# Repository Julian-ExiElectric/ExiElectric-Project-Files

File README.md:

# ExiElectric-Project-Files
Completed projects to be stored

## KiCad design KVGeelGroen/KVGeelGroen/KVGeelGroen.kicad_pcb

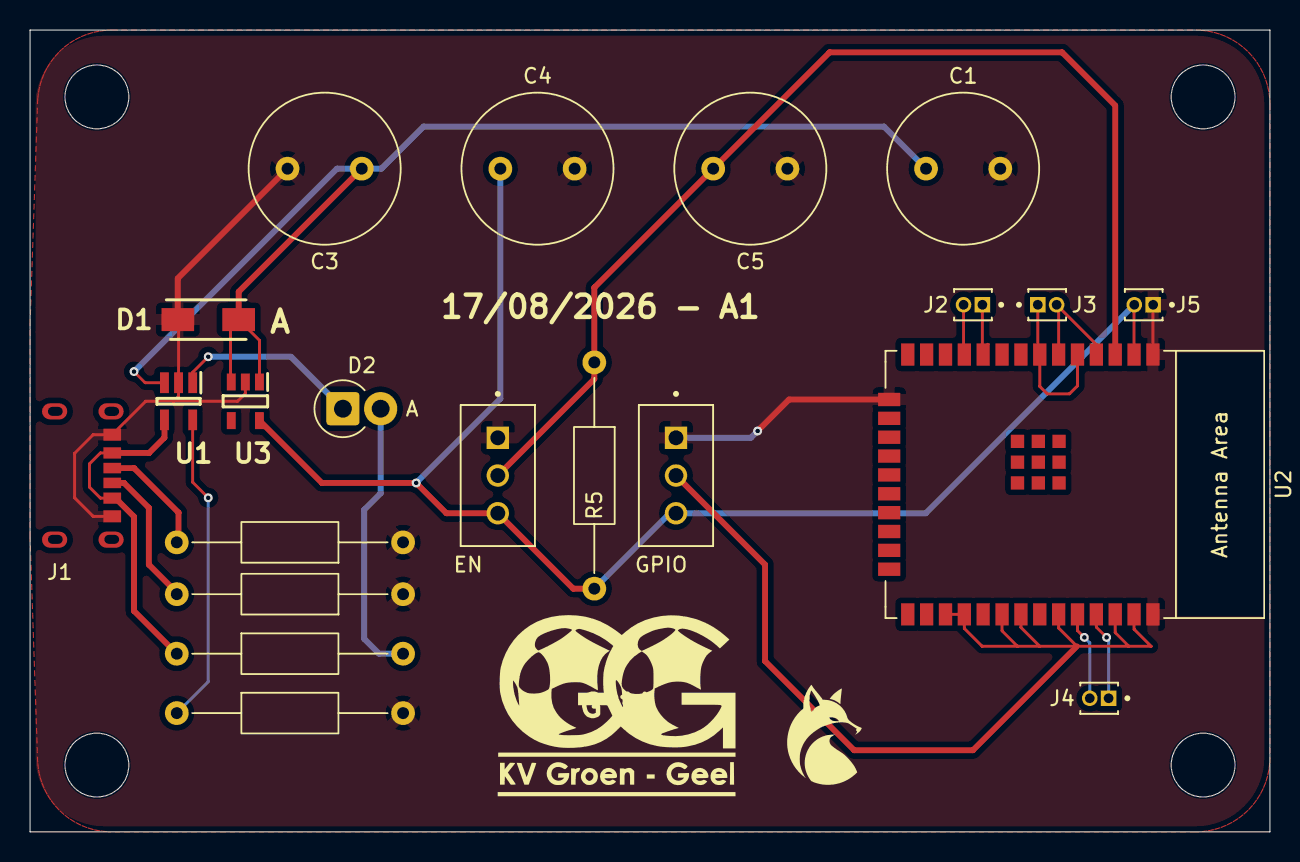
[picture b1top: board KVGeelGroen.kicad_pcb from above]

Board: 2 copper layers, 83.5 x 54.0 mm, 22 parts (0 on the bottom side), 17 nets.

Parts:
1: LOGO; CuteFox
C1: 5.6uF; C_Radial_D10.0mm_H12.5mm_P5.00mm
C3, C4, C5: 1uF; C_Radial_D10.0mm_H12.5mm_P5.00mm
D1: SMAJ5.0A-E3_61
D2: TEMP; D_DO-15_P2.54mm_Vertical_AnodeUp
EN: ATE1D-2M3-10-Z; SW_ATE1D-2M3-10-Z
GPIO: ATE1D-2M3-10-Z; SW_ATE1D-2M3-10-Z
J1: USB-C-MOLEX; 2171750001_MOL
J2, J3, J4, J5: M50-3530242; HARWIN_M50-3530242
R1: 2K; R_Axial_DIN0207_L6.3mm_D2.5mm_P15.24mm_Horizontal
R2: 75; R_Axial_DIN0207_L6.3mm_D2.5mm_P15.24mm_Horizontal
R3, R4: 5.1K; R_Axial_DIN0207_L6.3mm_D2.5mm_P15.24mm_Horizontal
R5: 10K; R_Axial_DIN0207_L6.3mm_D2.5mm_P15.24mm_Horizontal
U1: MCP73831T-2ACI_OT; MCP73831
U2: ESP32-WROOM-E; ESP32-WROOM-32E
U3: AP2112K-3V3; AP2112K

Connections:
+3V3: C4.1, EN.3, GPIO.3, J5.2, R5.2, U2.2 (3V3), U3.5 (VOUT)
+BATT: C1.1, C3.1, D1.2 (A), U1.3 (VBAT), U3.1 (VIN), U3.3 (EN)
GND: C1.2, C3.2, C4.2, C5.1, D1.1 (K), EN.1, GPIO.1, J1.A12 (GND_2), J1.B12 (GND), J5.1, R1.2, R3.1, R4.1, U1.2 (VSS), U2.1 (GND), U2.15 (GND), U2.38 (GND), U3.2 (GND)
unnamed: D2.2 (A), R2.2
unnamed: D2.1 (K), U1.1 (STAT)
unnamed: J1.A5 (CC1), R3.2
unnamed: J1.B5 (CC2), R4.2
unnamed: R1.1, U1.5 (PROG)
unnamed: J2.1, U2.10 (DAC_1/ADC2_CH8/GPIO25)
unnamed: J2.2, U2.11 (DAC_2/ADC2_CH9/GPIO26)
unnamed: C5.2, EN.2, R5.1, U2.3 (EN/CHIP_PU)
unnamed: GPIO.2, U2.27 (GPIO16), U2.28 (GPIO17), U2.30 (GPIO18), U2.31 (GPIO19), U2.33 (GPIO21), U2.36 (GPIO22), U2.37 (GPIO23)
unnamed: J3.2, U2.4 (SENSOR_VP/GPIO36/ADC1_CH0), U2.6 (GPIO34/ADC1_CH6)
unnamed: J3.1, U2.5 (SENSOR_VN/GPIO39/ADC1_CH3), U2.7 (GPIO35/ADC1_CH7)
unnamed: J4.2, U2.34 (U0RXD/GPIO3)
unnamed: J4.1, U2.35 (U0TXD/GPIO1)
VBUS: J1.A9 (VBUS_2), J1.B9 (VBUS), R2.1, U1.4 (VDD)

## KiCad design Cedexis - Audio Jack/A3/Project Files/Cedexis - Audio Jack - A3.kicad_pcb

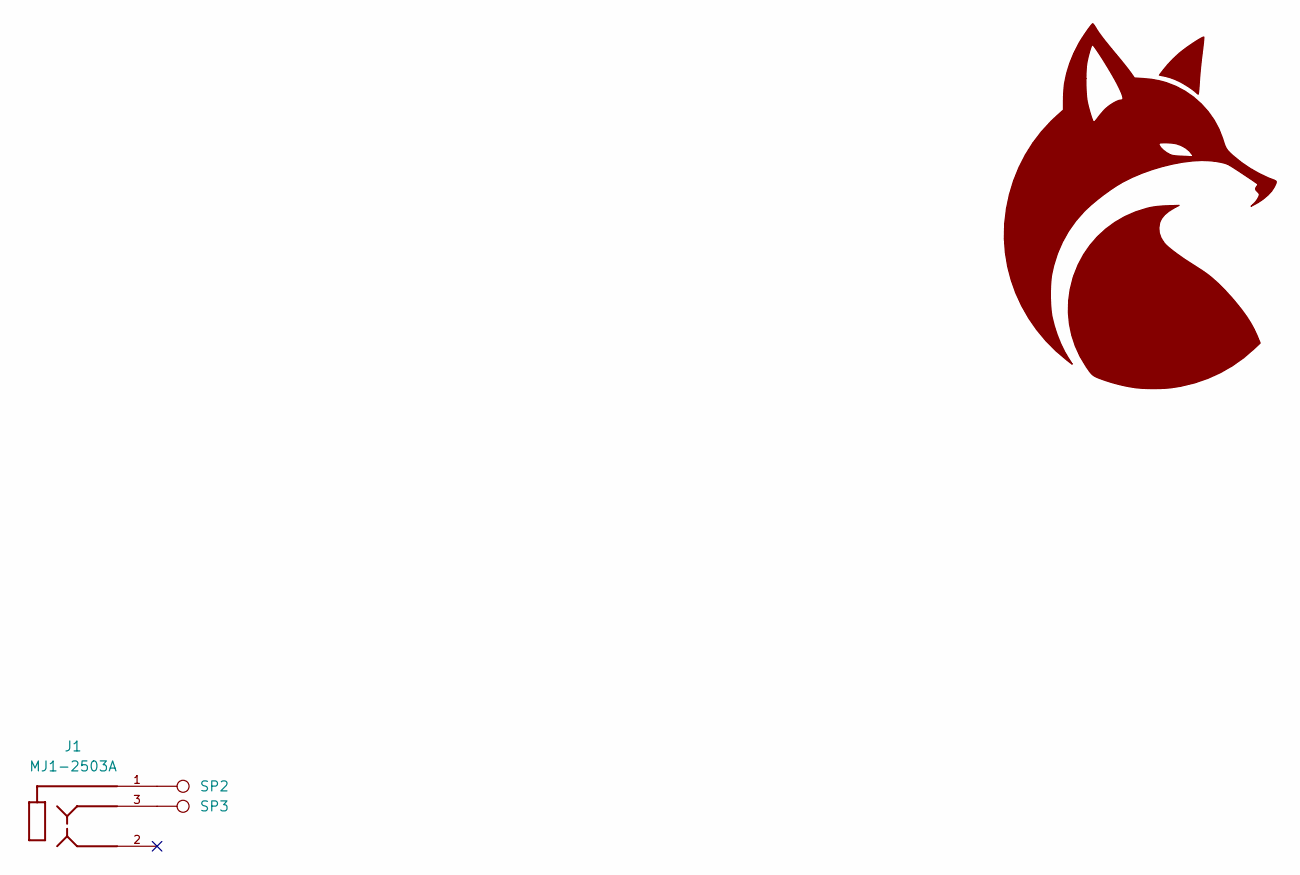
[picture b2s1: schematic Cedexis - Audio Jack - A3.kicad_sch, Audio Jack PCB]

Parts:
1: LOGO; CuteFox
J1: MJ1-2503A; PARTREV 1.05
SP2, SP3: TestPoint; TestPoint_THTPad_2.0x2.0mm_Drill1.0mm

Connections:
unnamed: J1.1, SP2.1 (1_1)
unnamed: J1.3, SP3.1 (1_1)

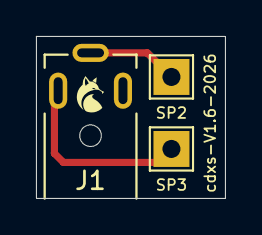
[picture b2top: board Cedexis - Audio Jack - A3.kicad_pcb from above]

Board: 2 copper layers, 10.5 x 9.0 mm, 4 parts (0 on the bottom side), 2 nets.

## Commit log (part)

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2026-06-23 Cedexis - Audio Jack - A1
